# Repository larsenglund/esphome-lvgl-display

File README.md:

ESPHome LVGL display for Home Assistant

Extends https://github.com/agillis/esphome-modular-lvgl-buttons (Copyright (c) 2024 Andrew Gillis)

## ESPHome Setup

1. Create/activate the project virtual environment (PowerShell example):
	```powershell
	& .\.venv\Scripts\Activate.ps1
	```
2. Make sure `pip` itself is current so it can pull the latest wheels:
	```powershell
	python -m pip install --upgrade pip
	```
3. Install the required Python packages (adds the ESPHome CLI entry point):
	```powershell
	python -m pip install -r packages.txt
	```
	If you prefer the dashboard UI, use `python -m pip install "esphome[dashboard]"` instead of the requirements file.
4. Verify the installation before building firmware:
	```powershell
	python -m esphome version
	```
	A semantic version string confirms the CLI is available; an error about `esphome.__main__` indicates the install did not succeed.
5. Build/flash your node:
	```powershell
	python -m esphome run custom_slider.yaml
	or
	python -m esphome run living-room-display.yaml --device living-room-display.local
	```

Troubleshooting tips:
- Ensure VS Code and ESPHome are both pointing to the same virtual environment (`Ctrl+Shift+P` → `Python: Select Interpreter`).
- Re-run step 3 if the environment changes or the dependency cache is cleared.

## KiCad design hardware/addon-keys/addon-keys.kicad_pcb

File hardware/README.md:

# Add-on boards for the Guition ESP32-S3-4848S040 (rev A)

Two KiCad 10 projects for a board that plugs into the 2x4 header on the back of the panel (where the 230 V power/relay module would go) and hangs below the display:
- `addon-keys`: three keys.
- `addon-encoders`: two rotary encoders.

They share everything except the bar below the display. Every KiCad file is generated by a script, using the pipeline from the LED controller project (`notes/cheap mcu AC632/rgbw-controller`). Edit the scripts, not the KiCad files, and rerun them.

**Status:** schematics, placement and routing done for both boards, DRC clean. Not ordered or built yet, so nothing is tested on a real board.
- **From Guition's own files:** the header pinout and the panel size.
- **Measured on a panel:** the header's position. The measurement agrees with a community replacement back cover to about 0.1 mm.
- **Placeholder:** the tab's outline.

**Revision:** both boards are rev A, marked on the bar's back silkscreen (`addon-keys rev A`, `addon-encoders rev A`) and in the schematic and PCB title blocks. `REV` in `addon/gen_addon.py` sets all of them. A board that changes after one has been made needs a new rev.

The overlays (User.Drawings layer) show the enclosure, its 5 mm border, and the 20 mm keycaps or the 25 mm knobs. The keys board's overlay also shows the enclosure's bottom border with the radar.

## Two boards

Keys and encoders are never fitted together. With the encoders as far apart as the enclosure allows, their pins and tab slots land on the switches' holes and pads in every rotation, about 0.16 mm short at best. So each gets its own board.

- **addon-keys:**
  - Three MX switches (HanElectricity CPG151101D13, clicky) in CPG151101S11-16 hot-swap sockets.
  - A warm-white 1206 LED in each switch's LED slot.
  - The HLK-LD2402 radar on a break-away piece centred below key 2. Snap it off for a build without the radar.
- **addon-encoders:**
  - Two Bourns PEC11R-4215F-S0024 encoders with push switches, for 25 mm knobs.
  - The radar between them. Leave it off for a build without the radar; there is no piece to snap off.
- **Both:**
  - CH32V003A4M6 co-processor, an I2C slave to the panel.
  - A bare SHT40 on a U-tab at the bar's right end.
  - 3.3 V LDO.
  - 5 V in from solder pads or an optional USB-C. The board feeds 5 V to the panel through the 2x4 header, so the panel's own USB is never connected.
  - Spare pins on solder pads (J5) and fourteen test points.

## Board (both)

- **Enclosure (front), as planned:**
  - **Width:** 82.9 mm, 2 mm a side narrower than the wall mount. The keys and encoders are still spaced for an 85.6 mm enclosure, so the side borders are 3.65 mm.
  - **Border:** 5 mm at the top and bottom, then a 1 mm gap around each keycap or knob.
  - **Height:** 32 mm for the keys and 37 mm for the encoders. With the radar, the keys board's enclosure has a radar section below that: 2 mm a side narrower again and half as tall (16 mm), 48 mm in all.
- **Bar (front, facing the room):**
  - **Width:** 79.4 mm, centred on the panel. Test-fitted, it sat flush with the panel's left edge and 0.9 mm short of its right edge. So it was trimmed 0.9 mm on the left to centre it, plus 1.1 mm on each side for the walls. It then lost 2 mm more on each side for the narrower enclosure, which leaves 1.75 mm beside it for the cover's walls and clearance.
  - **Height:** 30.9 mm on the keys board and 35.9 mm on the encoders board, ending 1.1 mm above the 5 mm bottom border.
- **SHT40 U-tab:**
  - **Where:** at the bar's right end, beside key 3 or encoder 2.
  - **Shape:** a 1 mm U-shaped slot cuts out a tongue 21 mm long: 3.1 mm wide on the keys board, 4.65 mm on the encoders board. It hangs from the top and is free at its lower end, near the bottom edge where the enclosure's vents should go.
  - **Parts:** the bare SHT40 near the free end, and C4 (100 nF) on the tongue.
  - **Distance from heat:** far from the regulator, the chip and the radar. On the keys board, key 3's LED, a few milliwatts, is the nearest heat source.
- **Panel:** 86.5 x 86.5 x 13.6 mm, from Guition's dimension drawing.
- **Panel header H1:** a 2x4 female socket with 2.54 mm pitch, its long axis vertical.
  - **Position (measured):** seen from the front, the header body starts 17 mm from the panel's left edge and 22 mm from its bottom edge. With a 5.08 x 10.16 mm body, its centre is 23.71 mm left of and 16.17 mm below the panel's centre.
  - **Cross-check:** the Printables replacement cover 1487412 has its window centred at 23.8 / 16.1 mm.
  - **Pinout (Guition schematic):** 1 GND, 2 GND, 3 IO40 (relay 1), 4 U0RXD, 5 IO2 (relay 2), 6 U0TXD, 7 IO1 (relay 3), 8 5V.
  - **Pin 1:** the top of the column nearer the panel's centre.
  - **No 3.3 V:** H1 has none, so the board has its own regulator.
  - **IO1/IO2/IO40:** they reach H1 through 0 Ω links R25-R27 on the panel. The alternative links R21-R23 route them to the audio amplifier instead.
- **H1 height:** the socket stands about 3 mm out of the panel's back, so the board's front sits 3.2 mm behind the panel's back (the wall mount allows for it).
- **J1:** the male header that plugs into H1. Its footprint numbers each pad like the H1 pin it mates with, so the schematic pin numbers are the panel's. SDA = IO1 (pin 7), SCL = IO2 (pin 5). IO40 and the ESP's UART0 (pins 3, 4, 6) go to the spare pads.
- **Spare pads and test points (back, along the bar's top edge below the tab, behind the enclosure's top border):**
  - **J5:** a row of 2.54 mm through-hole pads for wires or a header, labelled on the back. In order: IO40, RXD and TXD (the ESP's UART0, which carries its boot log), PA2 and PD7 (the co-processor's spare pins; PD7 doubles as NRST), and GND.
  - **TP1-TP8:** 1.5 mm pads on the back, 3 mm apart: 5V, 3V3, GND, SDA, SCL and the radar's TX, RX and OUT (labelled R-TX, R-RX, R-OUT). On the keys board the radar's three are in the order R-OUT, R-TX, R-RX, the order their tracks arrive in. They stay on the bar when the keys board's radar piece is snapped off.
  - **TP9-TP14:** 1.5 mm pads on the back for the keys' or encoders' own signals, each labelled beside it. They sit where the back has room next to those tracks, so they aren't all in the row:
    - **Keys board:** K1, K2 and K3 below the row, LED2 and LED3 above it on the tab, and LED1 further up the tab, between the co-processor and the resistors.
    - **Encoders board:** E1_SW, E1_B and E1_A in a second row below J5, E2_A and E2_B at the right-hand end of the row, and E2_SW above the 5V pad.
- **Alignment holes MH1 and MH2:** 2.2 mm, no copper, 37 mm left and right of the centre and 4.5 mm below the panel's bottom edge, for the wall mount's 2 mm pins.
- **Tab (behind the panel):**
  - **Size and position:** 28.5 mm wide. Its left edge stays clear of the stock back cover's screw near the panel's lower-left corner (front view, about 37 mm left of and 29 mm below the centre).
  - **Hook notch:** its lower-left corner is cut away, 3.6 mm across and 5.75 mm up from the panel's bottom edge, for the wall mount's lower-left clip hook (30.85 mm left of and 38.5 mm below the panel's centre). The resistor row starts right of it.
  - **Front:** the 2x4 header only.
  - **Back (wall side, inside the wall box):** the USB-C (opening at the tab's right edge), the 5 V wire pads, the LDO, the co-processor, the resistors and the programming pads. Keeping the heat sources here keeps them away from the SHT40.
- **Hand soldering:**
  - 1206 hand-solder pads.
  - SOT-223 regulator.
  - SOIC-16 with pads 0.8 mm longer than standard.
  - Through-hole headers and encoders.
  - The hot-swap socket pads are 2.5 x 2.55 mm.
  - The exception is the bare SHT40, a 1.5 mm DFN with its pads underneath. Its footprint has pads 0.5 mm longer than standard, so it can be tinned and reflowed from outside, but hot air or a hot plate is the reliable way. A small breakout could fit on the tongue instead if you prefer.

## Routing (both)

2 layers, 1 oz. `addon/route_addon.py` runs all of it.

- **Track widths:** `+5V` 0.5 mm, since it feeds the panel too. `+3V3` and GND 0.3 mm (about 100 mA). Signals 0.25 mm. Clearance 0.2 mm.
- **GND:** a pour on each side, joined by stitching vias about 7 mm apart. Every surface-mount GND pad has its own via, and J4's GND pad is tied to TP3 on the back, so signal tracks can't fence a pad off from the pours. Freerouting doesn't wire GND.
- **Vias:** tented on both sides. None inside pads, as those are soldered by hand.
- **SHT40 tongue:** routed by hand, with its own 0.25 mm tracks up the back and no pour on either side, so little heat reaches the sensor along the copper.
- **Everything else:** Freerouting, best of several runs, then a small A* router for anything left open. It runs on both sides of the board, including under the switches and encoders; the copper there is covered by solder mask.
- **TP9-TP14:** added to the routed boards afterwards, on or beside the tracks already there, with short tracks and one via (LED1's, on the keys board). A fresh `route_addon.py` run puts them in the same spots and routes them like any other net.

## Keys board

- **Keys:** three, spread evenly inside the border, so they are 26.8 mm apart, centred 16 mm below the panel's bottom edge. Switches turned 90 degrees, so the socket pads on the back stay inside each switch's outline and the LED slot faces right.
- **Radar (break-away piece):**
  - **Position:** centred on the bar, under key 2, as close to the keys as the switches allow. Its top edge is 0.3 mm below key 2's switch body, so its top 2.7 mm sit behind keycap 2 and the gap around it. It can't come any closer: the switch body is in the way, and between the keys there is only 12.8 mm for the 20 mm module. The bottom border with the radar shrinks to about 17.4 mm.
  - **Effect of key 2:** key 2's switch stands about 11.6 mm tall right at the radar's top edge. That shades part of its upward view; the forward view isn't affected.
  - **Break line:** steps up under the radar to just below key 2's socket, notching the middle of the bar's bottom edge, with a 1 mm gap down each side of the piece. With the piece snapped off, the notch hides behind the 5 mm border.
  - **Bridges:** three 4 mm bridges with 0.5 mm mouse-bite holes on the bar's edge line: one across each side gap and one across the top gap, right of key 2's hot-swap socket (there is no room for one on its left). The left bridge, by the radar's header column, has only its two end holes, and the radar's five tracks cross it between them, straight and all on the back: score the back with a knife before snapping, and clean up the track ends so they can't short. The pours stay off all three bridges.
  - **Radar tracks:** routed by hand from the header, across the bridge and up the back of the bar left of key 2, then along above the key sockets to the test points. The radar's GND drops to the front pour through a via just left of the bridge.
  - **Orientation:** turned 180 degrees from Hi-Link's figure 6-1, so all five header pins land on the piece; Hi-Link's manual says this orientation is equivalent. The module floats over the notch and the bridges on its 2.5 mm header.
- **SHT40:** sits below the 1 mm gap between keycap 3 and the border.

## Encoders board

- **Encoders:** as far apart as the enclosure allows. Across, it is 5 mm border, 1 mm gap, knob, the space between, knob, 1 mm gap, 5 mm border, so the centres are 18.5 mm in from each end of the enclosure and 48.6 mm apart.
- **Height:** the same from top to bottom, so the enclosure is 37 mm tall and the bar 5 mm taller than the keys board's. The encoders are centred 18.5 mm below the panel's bottom edge, 2.5 mm lower than the keys.
- **Radar:** midway between the encoders and level with them, oriented as in Hi-Link's figure 6-1 (header column on the right). Seen from the front, the knobs clear its sides by about 1.8 mm. Plastic knobs are best; metal ones beside the radar would shade its view to the sides.
- **SHT40:** below and to the right of knob 2, in the enclosure's lower-right corner, with C4 above it. Both are clear of the knob.

## Pin map (CH32V003A4M6)

| Pin | Keys board | Encoders board |
|---|---|---|
| PC1 / PC2 | I2C SDA / SCL to the panel (GPIO1 / GPIO2), 4.7k pull-ups | same |
| PD5 / PD6 | USART1 TX / RX to the radar | same |
| PD4 | radar OUT (presence) | same |
| PC6 / PC7 / PC0 | LED 1 / 2 / 3, PWM on TIM1 CH1-CH3 (remap 1) through 100 R | encoder 1 A / B, encoder 2 A |
| PC3 / PA1 / PC4 | key 1 / 2 / 3 | encoder 1 push / encoder 2 B / encoder 2 push |
| PD1 | SWIO (WCH-LinkE on J4) | same |
| PD7, PA2 | spare, on J5 | same |

The two boards use the same pins, so one firmware can serve both. It needs to know which board it's on.

## Parts

| Ref | Part | LCSC | Board |
|---|---|---|---|
| U1 | LDL1117S33R, 3.3 V LDO, SOT-223 | C435835 | both |
| U2 | CH32V003A4M6, SOP-16 | C5346357 | both |
| U3 | HLK-LD2402 radar | C48935081 | both, optional |
| SW1-SW3 | CPG151101S11-16 hot-swap socket + CPG151101D13 switch | C41430893 + C49234235 | keys |
| D1-D3 | warm-white 1206 LED, 2800-3400 K (XINGLIGHT XL-3216WWC) | C965830 | keys |
| R5-R7 | 100 R 1206 | C17901 | keys |
| ENC1, ENC2 | Bourns PEC11R-4215F-S0024 | C143790 | encoders |
| C1, C2 | 10 uF 1206 | C7467044 | both |
| C3 | 100 nF 1206 | C93194 | both |
| R3, R4 | 4.7k 1206 (I2C pull-ups) | C17936 | both |
| J1 | 2x4 male header, 2.54 mm, into the panel's H1 (pin length: see below) | C492421 | both |
| J2 | 5 V wire pads | | both |
| J3, R1, R2 | USB-C 6P power-only, 4.7k CC pull-downs (5.1k +-20 %) | C456012, C17936 | both, optional |
| J4 | programming pads: SWIO, 3V3, GND | | not fitted |
| J5 | spare pads: IO40, RXD, TXD, PA2, PD7, GND | | not fitted |
| TP1-TP14 | test points, bare 1.5 mm pads | | both, no part |
| U5 | Sensirion SHT40-AD1B-R2 (I2C 0x44), DFN-4 1.5 x 1.5 mm. Not in LCSC's shop: see below | C2909890, for JLCPCB fitting it; DigiKey 1649-SHT40-AD1B-R2CT-ND to solder by hand | both |
| C4 | 100 nF 1206, on the SHT40 tab | C93194 | both |

## Before ordering

- **Header position:** worth a careful second measurement before ordering, since a board-to-board connector leaves no slack. It is set by `HDR_DX` and `HDR_DY` in `place_addon.py`.
- **Panel links:** check that R25-R27 (0 Ω) are fitted on your panels, so IO1 and IO2 actually reach H1. That is likely on relay units and should be checked on ones bought without relays.
- **Pin length:** H1 stands about 3 mm out of the panel's back and the board's front is 3.2 mm behind that back, so H1's mouth is only 0.2 mm from the board's front. That leaves no room for a header's 2.5 mm plastic spacer or for a solder fillet on the front. So use a standard 2x4 header (C492421: 6 mm pins, 2.5 mm spacer, 3 mm tails) like this: push the tails in from the front, solder on the back, pull the spacer off over the pin tips, then cut the pins to about 6 mm past the board's front. That goes about as deep into H1 as a normal header would. H1's actual depth hasn't been measured, so check it with a loose pin before cutting. A long-pin header with its spacer on the back, such as C7128766 (8.13 mm pins), also reaches, but it has to be soldered on the front or with the spacer held off the back.
- **Mechanics:** check how the board gets past the frame rim, and the outline.
- **Radar pinout:** check the module's print against 1 VCC, 2 OUT, 3 GND, 4 TX, 5 RX (Hi-Link manual p. 7).
- **Radar header:** the radar's pins must come out of the non-antenna side.
- **LED fit:** check that a 1206 LED fits in the switch's LED slot. From the datasheet the slot is about 9.4 x 2.7 mm.
- **SHT40:** LCSC's shop doesn't sell Sensirion's part. C2909890 only works for having JLCPCB fit it (16,586 in its parts data on 2026-11-02). To solder it by hand, buy DigiKey 1649-SHT40-AD1B-R2CT-ND: cut tape, 3,379 in stock and 17.11 kr each for 5 or more on 2026-11-02. Either plan how to solder it (hot air or a hot plate) or have JLCPCB fit just that part. LCSC does sell look-alikes named SHT40, untested here. The datasheet of Nyfea's SHT40-N-NF (C54946589, about $1) states the same address (0x44), pin order and measure command (0xFD); C55170371 and C54823945 are others.
- **Alignment test:** print `addon-keys/mockup/addon-keys-alignment.stl` or `addon-encoders/mockup/addon-encoders-alignment.stl` (`tools/export_jig_stl.py`), hot-glue a 2x4 header into it and try it on a panel. Its pin holes are opened up for printing: 1.7 mm for the 2.54 mm headers (J1, J4, J5, radar), 1.5 mm for the encoder pins, the encoder tab slots by 0.2 mm, and 2.9 mm for the wall mount's 2.0 mm alignment pins (MH1, MH2; 2.2 mm on the board).
- **JLCPCB's limits (checked against its capabilities page, 2026-10-31):** tracks, clearances, vias and annular rings are all inside them, with no surcharge for via size. Three things fall outside its guidance: the silkscreen labels are 0.8 mm tall against a 1.0 mm minimum (still 0.15 mm lines, so they should print, just small); the encoders' plated tab slots (1.9 x 2.7 mm) are shorter than the twice-their-width it asks for; and the keys board's mouse-bite bridges are 4 mm against 5 mm for its panel tabs, though it doesn't say that applies inside one design.
- **Parts lists:** [addon-keys/lcsc-order-5.csv](addon-keys/lcsc-order-5.csv) and [addon-encoders/lcsc-order-5.csv](addon-encoders/lcsc-order-5.csv) are LCSC BOM uploads for 5 boards with spares, checked against LCSC's stock, minimums and prices on 2026-11-02 (the keys board's LEDs on 2026-11-17). They come to about $14 and $33, plus $15 if you take the 5 radars on each list: LCSC only has 11, so delete that line for any you already have. Not on them: U5 (LCSC doesn't sell it; see above), keycaps and knobs, and pins for the radar if yours comes without. J4 and J5 aren't fitted.
- **Order files:** `tools/export_gerbers.py` writes `addon-<board>/production/addon-<board>-gerbers.zip` (git-ignored). Export again after any change to the board. There's no placement file yet, in case JLCPCB is to fit any parts.
- **Firmware:** still to write: the CH32V003 firmware and the ESPHome component that talks to it.

## Files

| File | What |
|---|---|
| `addon/gen_addon.py` | Schematic for either board (`keys` or `encoders`): parts, values, LCSC numbers, nets |
| `addon/place_addon.py` | Board for either board: outline (with the U-tab, and the keys board's break-away piece), placement, labels, DRC rules, enclosure overlay, pours, the GND vias and the tracks routed by hand |
| `addon/route_addon.py` | Routes either board from scratch with the tools below |
| `addon/sym-lib-table`, `addon/fp-lib-table` | Library tables, copied into each project by `gen_addon.py` |
| `addon-keys/`, `addon-encoders/` | Generated KiCad projects |
| `addon-*/renders/` | 3D renders (top, bottom, angled) and the enclosure overlay |
| `lib/addon.*` | Symbols, footprints and STEP models |
| `tools/addon_lib.py` | Makes the radar symbol and footprint, the hot-swap MX, PEC11R, SHT40 and hand-solder SOIC-16 footprints, the mouse bites, and the USB-C footprint |
| `tools/export_jig_stl.py` | The fit-test STL, with the pin holes opened up for printing |
| `tools/stitch.py` | Stitching vias between the GND pours, after routing |
| `tools/export_gerbers.py` | The Gerber and drill zip to upload to the fab |
| `tools/autoroute.py`, `tools/finish_route.py`, `tools/fanout.py` | Freerouting, the A* router for what it leaves open, and a via for each SMD GND pad, from fablights. These know these boards aren't rectangles |
| `tools/` | schgen, pcbbuild, netcheck, import_lcsc, render3d, from the LED controller project |

## Rebuild

Run from the repo root. `KPY` is KiCad's own Python, used for everything that imports pcbnew. `VENV` is the fablights venv, which has easyeda2kicad. Routing needs `freerouting-*.jar` and a Java 25 runtime (not committed) in `hardware/tools/ext/` or in a fablights checkout next to this repo.

**`place_addon.py` starts the board over, routing included.** After changing anything on the board, route it again. Freerouting varies from run to run, so the tracks will differ each time: look through the result before ordering.

```bash
KPY="/c/Program Files/KiCad/10.0/bin/python.exe"
CLI="/c/Program Files/KiCad/10.0/bin/kicad-cli.exe"
VENV=/c/Users/englund/Documents/GitHub/fablights/tools/.venv/Scripts/python.exe

"$VENV" hardware/tools/import_lcsc.py C456012 C41430893 C49234235 C143790   # STEP models (once)
python hardware/tools/addon_lib.py                                         # own symbols and footprints
"$CLI" fp upgrade --force hardware/lib/addon.pretty
for B in keys encoders; do
  P=hardware/addon-$B/addon-$B
  python hardware/addon/gen_addon.py $B                                    # schematic
  "$CLI" sch upgrade --force $P.kicad_sch
  python hardware/tools/netcheck.py $P.kicad_sch                           # ERC + single-pin nets
  python hardware/addon/route_addon.py $B                                  # board, placement and routing (a few minutes)
  "$CLI" pcb drc --schematic-parity --severity-all -o drc-$B.rpt $P.kicad_pcb
  "$KPY" hardware/tools/render3d.py addon-$B                               # renders/
  "$KPY" hardware/tools/export_jig_stl.py $B                               # fit-test STL (git-ignored)
  python hardware/tools/export_gerbers.py $B                               # Gerbers and drill for the fab (git-ignored)
done
```

**Don't run `kicad-cli sym upgrade` on `lib/addon.kicad_sym`:** kicad-cli 10.0.6 then crashes loading any schematic that embeds the upgraded radar symbol.

**Expected DRC result:**
- `lib_footprint_issues` (32 and 26), which kicad-cli prints because there's no global footprint library table on this machine.
- Nothing else. Rules in `addon-keys.kicad_dru` allow the keys board's intended overlaps: the LEDs inside the switches, and the radar over key 2's edge and the break line. The encoders board needs none.

## Sources

- Guition's support package for the panel, with the schematic (`5-IO pin distribution/2.png`), the dimension drawing (`3-Structure_Diagram/Dimensions.jpg`) and the spec PDF: <https://pan.jczn1688.com/1/ESP32%20module/4.0inch_ESP32-4848S040.zip>
- Header position measured on a panel and cross-checked against the Printables replacement back cover 1487412; board photos at <https://homeding.github.io/boards/esp32s3/panel-4848S040.htm>
- Hi-Link HLK-LD2402 manual (pins p. 7, drawing p. 37, orientation pp. 33-35): <https://www.manualslib.com/manual/4392645/Hi-Link-Hlk-Ld2402.html>
- Bourns PEC11R datasheet: <https://www.bourns.com/docs/Product-Datasheets/PEC11R.pdf>
- HanElectricity CPG151101D13 and CPG151101S11-16 drawings, from LCSC (C49234235, C41430893)

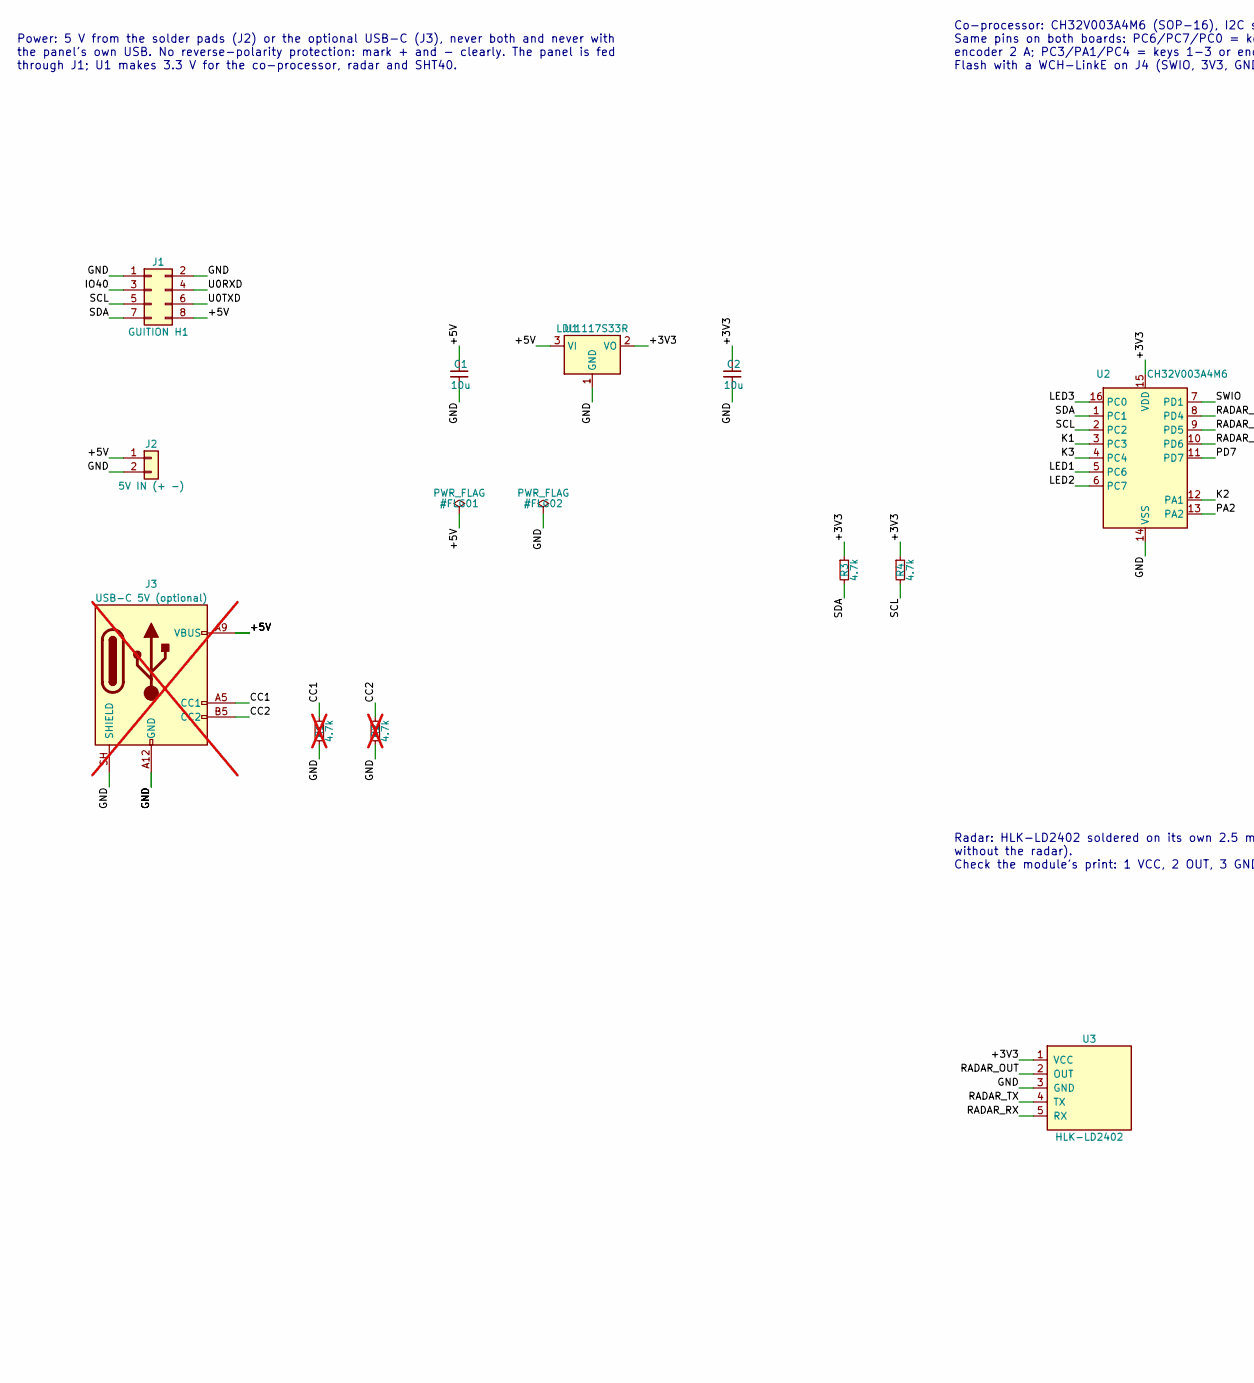
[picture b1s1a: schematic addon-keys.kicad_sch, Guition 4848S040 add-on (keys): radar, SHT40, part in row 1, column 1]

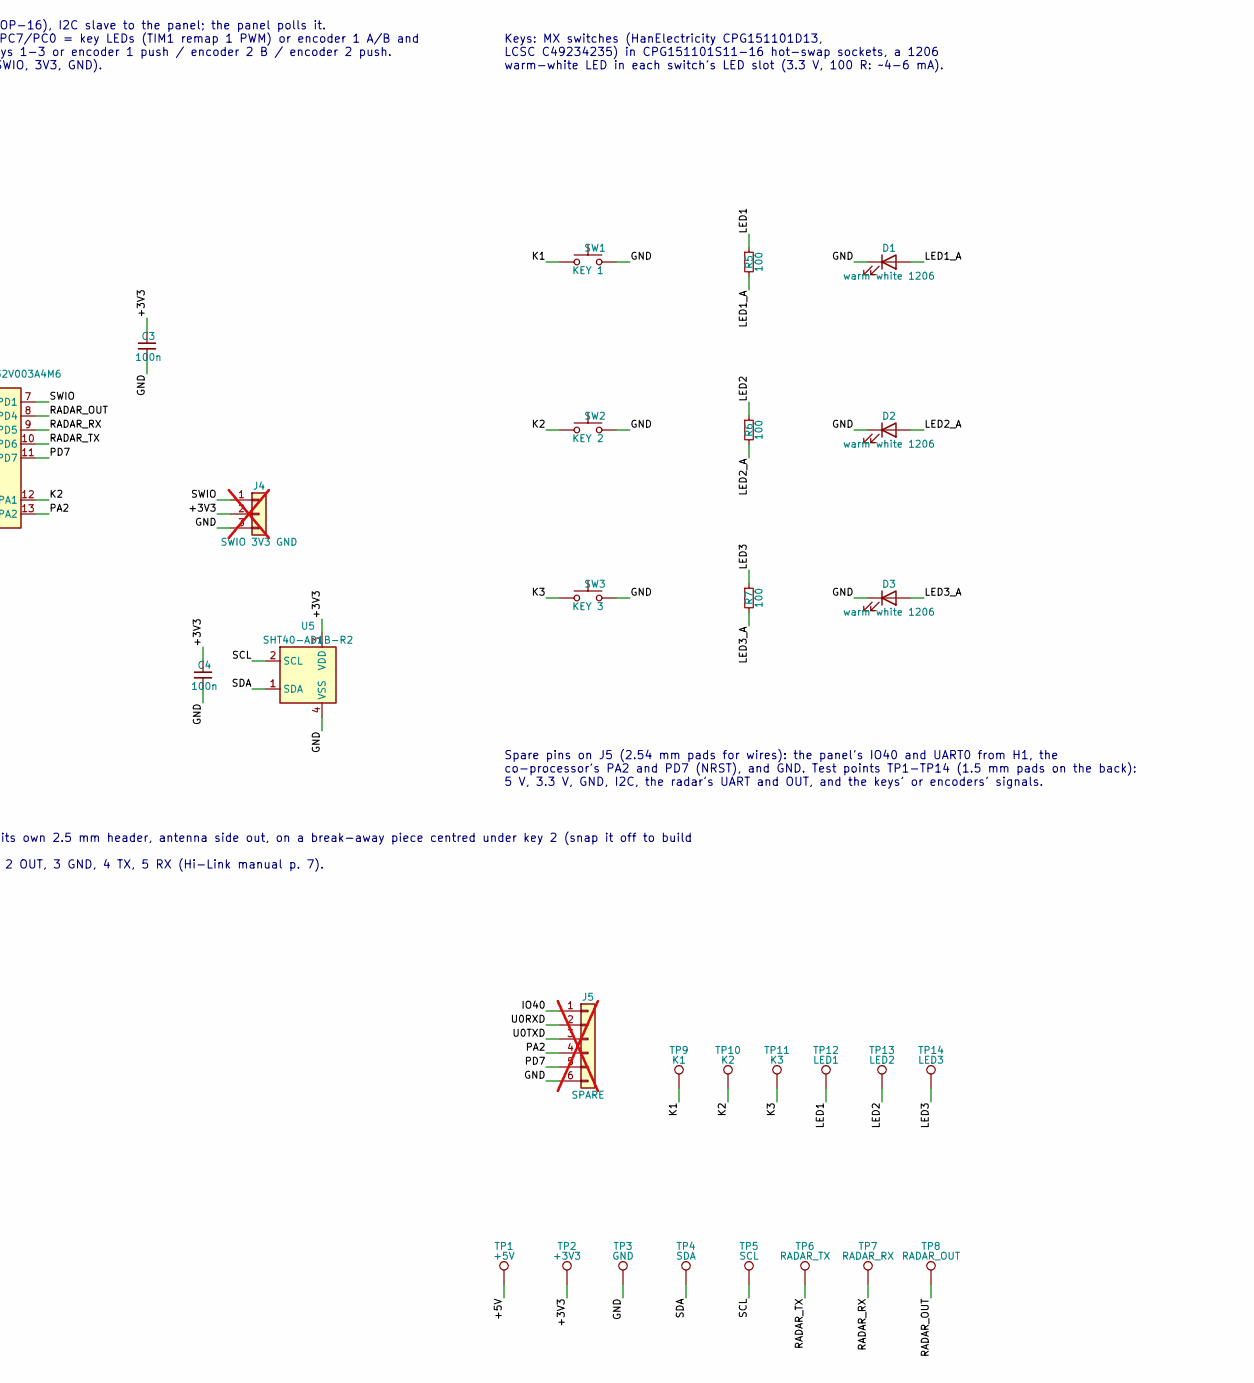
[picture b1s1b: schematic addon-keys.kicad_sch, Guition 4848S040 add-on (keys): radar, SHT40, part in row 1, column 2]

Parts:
C1, C2: 10u; C_1206_3216Metric_Pad1.33x1.80mm_HandSolder; LCSC C7467044
C3, C4: 100n; C_1206_3216Metric_Pad1.33x1.80mm_HandSolder; LCSC C93194
D1, D2, D3: warm white 1206; LED_1206_3216Metric_Pad1.42x1.75mm_HandSolder; LCSC C965830
J1: GUITION H1; Guition_H1_2x04_P2.54mm_Mating; LCSC C492421
J2: 5V IN (+ -); SolderWire-0.5sqmm_1x02_P4.6mm_D0.9mm_OD2.1mm
J3: USB-C 5V (optional); USB_C_Receptacle_SHOU-HAN_TYPE-C-6P; LCSC C456012; not fitted
J4: SWIO 3V3 GND; PinHeader_1x03_P2.54mm_Vertical; not fitted
J5: SPARE; PinHeader_1x06_P2.54mm_Vertical; not fitted
R1, R2: 4.7k; R_1206_3216Metric_Pad1.30x1.75mm_HandSolder; LCSC C17936; not fitted
R3, R4: 4.7k; R_1206_3216Metric_Pad1.30x1.75mm_HandSolder; LCSC C17936
R5, R6, R7: 100; R_1206_3216Metric_Pad1.30x1.75mm_HandSolder; LCSC C17901
SW1: KEY 1; SW_MX_Hotswap_CPG151101S11; LCSC C41430893
SW2: KEY 2; SW_MX_Hotswap_CPG151101S11; LCSC C41430893
SW3: KEY 3; SW_MX_Hotswap_CPG151101S11; LCSC C41430893
TP1: +5V; TestPoint_Pad_D1.5mm
TP2: +3V3; TestPoint_Pad_D1.5mm
TP3: GND; TestPoint_Pad_D1.5mm
TP4: SDA; TestPoint_Pad_D1.5mm
TP5: SCL; TestPoint_Pad_D1.5mm
TP6: RADAR_TX; TestPoint_Pad_D1.5mm
TP7: RADAR_RX; TestPoint_Pad_D1.5mm
TP8: RADAR_OUT; TestPoint_Pad_D1.5mm
TP9: K1; TestPoint_Pad_D1.5mm
TP10: K2; TestPoint_Pad_D1.5mm
TP11: K3; TestPoint_Pad_D1.5mm
TP12: LED1; TestPoint_Pad_D1.5mm
TP13: LED2; TestPoint_Pad_D1.5mm
TP14: LED3; TestPoint_Pad_D1.5mm
U1: LDL1117S33R; SOT-223-3_TabPin2; LCSC C435835
U2: CH32V003A4M6; SOIC-16_3.9x9.9mm_P1.27mm_HandSolder; LCSC C5346357
U3: HLK-LD2402; LCSC C48935081
U5: SHT40-AD1B-R2; Sensirion_DFN-4_1.5x1.5mm_P0.8mm_SHT4x_HandSolder; LCSC C2909890

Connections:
/+3V3: C2.1, C3.1, C4.1, J4.2, R3.1, R4.1, TP2.1, U1.2 (VO), U2.15 (VDD), U3.1 (VCC), U5.3 (VDD)
/+5V: C1.1, J1.8, J2.1, J3.A9 (VBUS), J3.B9 (VBUS), TP1.1, U1.3 (VI)
/CC1: J3.A5 (CC1), R1.1
/CC2: J3.B5 (CC2), R2.1
/GND: C1.2, C2.2, C3.2, C4.2, D1.1 (K), D2.1 (K), D3.1 (K), J1.1, J1.2, J2.2, J3.A12 (GND), J3.B12 (GND), J3.SH (SHIELD), J4.3, J5.6, R1.2, R2.2, SW1.2, SW2.2, SW3.2, TP3.1, U1.1 (GND), U2.14 (VSS), U3.3 (GND), U5.4 (VSS)
/IO40: J1.3, J5.1
/K1: SW1.1, TP9.1, U2.3 (PC3)
/K2: SW2.1, TP10.1, U2.12 (PA1)
/K3: SW3.1, TP11.1, U2.4 (PC4)
/LED1: R5.1, TP12.1, U2.5 (PC6)
/LED1_A: D1.2 (A), R5.2
/LED2: R6.1, TP13.1, U2.6 (PC7)
/LED2_A: D2.2 (A), R6.2
/LED3: R7.1, TP14.1, U2.16 (PC0)
/LED3_A: D3.2 (A), R7.2
/PA2: J5.4, U2.13 (PA2)
/PD7: J5.5, U2.11 (PD7)
/RADAR_OUT: TP8.1, U2.8 (PD4), U3.2 (OUT)
/RADAR_RX: TP7.1, U2.9 (PD5), U3.5 (RX)
/RADAR_TX: TP6.1, U2.10 (PD6), U3.4 (TX)
/SCL: J1.5, R4.2, TP5.1, U2.2 (PC2), U5.2 (SCL)
/SDA: J1.7, R3.2, TP4.1, U2.1 (PC1), U5.1 (SDA)
/SWIO: J4.1, U2.7 (PD1)
/U0RXD: J1.4, J5.2
/U0TXD: J1.6, J5.3

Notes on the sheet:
Spare pins on J5 (2.54 mm pads for wires): the panel's IO40 and UART0 from H1, the co-processor's PA2 and PD7 (NRST), and GND. Test points TP1-TP14 (1.5 mm pads on the back): 5 V, 3.3 V, GND, I2C, the radar's UART and OUT, and the keys' or encoders' signals.
Power: 5 V from the solder pads (J2) or the optional USB-C (J3), never both and never with the panel's own USB. No reverse-polarity protection: mark + and - clearly. The panel is fed through J1; U1 makes 3.3 V for the co-processor, radar and SHT40.
Radar: HLK-LD2402 soldered on its own 2.5 mm header, antenna side out, on a break-away piece centred under key 2 (snap it off to build without the radar). Check the module's print: 1 VCC, 2 OUT, 3 GND, 4 TX, 5 RX (Hi-Link manual p. 7).
Co-processor: CH32V003A4M6 (SOP-16), I2C slave to the panel; the panel polls it. Same pins on both boards: PC6/PC7/PC0 = key LEDs (TIM1 remap 1 PWM) or encoder 1 A/B and encoder 2 A; PC3/PA1/PC4 = keys 1-3 or encoder 1 push / encoder 2 B / encoder 2 push. Flash with a WCH-LinkE on J4 (SWIO, 3V3, GN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
Keys: MX switches (HanElectricity CPG151101D13, LCSC C49234235) in CPG151101S11-16 hot-swap sockets, a 1206 warm-white LED in each switch's LED slot (3.3 V, 100 R: ~4-6 mA).

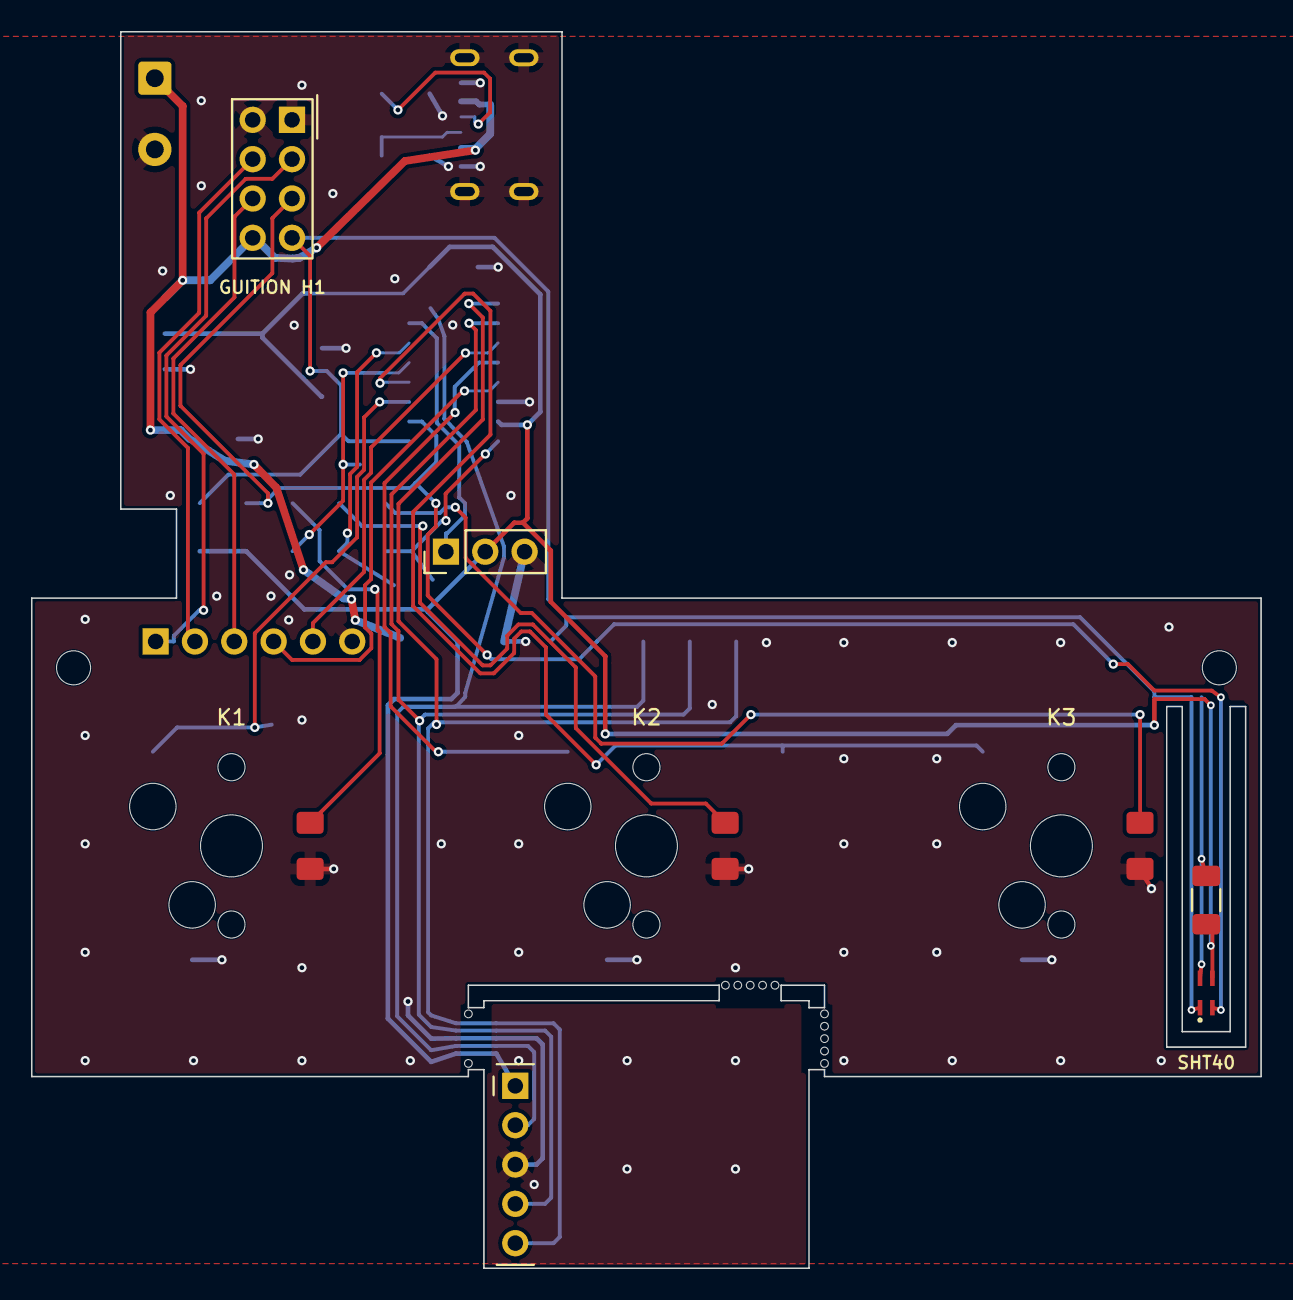
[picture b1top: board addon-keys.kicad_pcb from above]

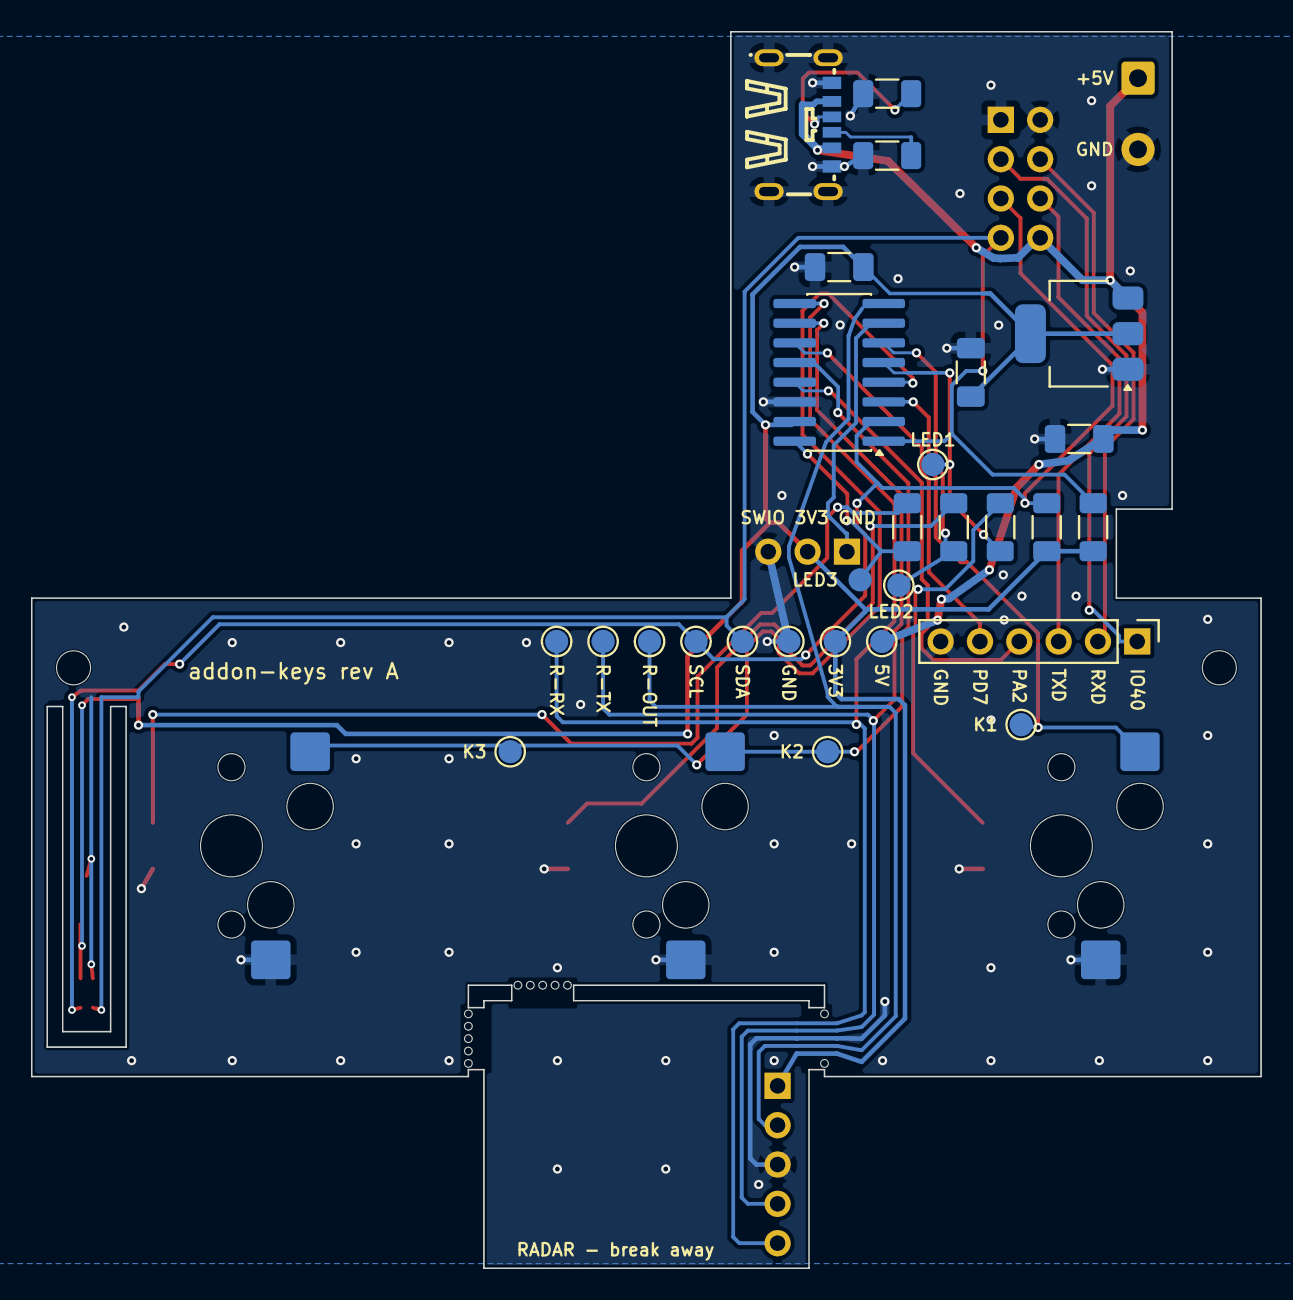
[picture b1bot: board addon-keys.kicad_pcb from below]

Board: 2 copper layers, 79.4 x 79.9 mm, 45 parts (28 on the bottom side), 25 nets.

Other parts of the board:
MB1: MouseBite_4mm_Traces
MB2, MB3: MouseBite_4mm
MH1, MH2: MountingHole_2.2mm_M2

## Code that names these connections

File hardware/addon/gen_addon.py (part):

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3.3 V LDO, 5 V in from solder pads or an optional USB-C, and the panel powered
through the header. The co-processor's pins do the same jobs on both boards
(one firmware, told which board it is on). The header's unused pins (IO40,
UART0) and the co-processor's spare PA2/PD7 come out on pads (J5); test points
on 5 V, 3.3 V, GND, I2C, the radar's lines and the keys' or encoders' signals.
Hand-solder parts throughout (1206, SOT-223, SOIC-16), apart from the SHT40
(1.5 mm DFN: hot air, or extended pads and patience).
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

# Co-processor pins for the keys or encoders (same pins on both boards):
# PC6/PC7/PC0 are TIM1 CH1-CH3 (remap 1): hardware PWM for the key LEDs, and PC6/PC7 are
# TIM1's encoder-mode inputs for encoder 1.
IO = {"keys": {"PC6": "LED1", "PC7": "LED2", "PC0": "LED3", "PC3": "K1", "PA1": "K2", "PC4": "K3"},
      "encoders": {"PC6": "E1_A", "PC7": "E1_B", "PC0": "E2_A", "PC3": "E1_SW", "PA1": "E2_B",
                   "PC4": "E2_SW"}}[BUILD]

# --- power: 5 V in, panel header, 3.3 V LDO -------------------------------------------------
sch.text("Power: 5 V from the solder pads (J2) or the optional USB-C (J3), never both and never with\n"
         "the panel's own USB. No reverse-polarity protection: mark + and - clearly. The panel is fed\n"
         "through J1; U1 makes 3.3 V for the co-processor, radar and SHT40.", (20, 20), size=1.5)
# Pin numbers are the panel's H1 (Guition schematic): 1/2 GND, 3 IO40 (relay 1), 4 U0RXD,
# 5 IO2 (relay 2), 6 U0TXD, 7 IO1 (relay 3), 8 5V. No 3.3 V on H1. IO40/IO2/IO1 reach H1
# through 0R links R25-R27 on the panel (R21-R23 instead send them to the audio amplifier).
sch.add("Connector_Generic:Conn_02x04_Odd_Even", "J1", "GUITION H1", (45, 60),
        fp="addon:Guition_H1_2x04_P2.54mm_Mating", lcsc="C492421",
        pins={"1": "GND", "2": "GND", "3": "IO40", "4": "U0RXD", "5": "SCL", "6": "U0TXD", "7": "SDA",
              "8": "+5V"},
        fields={"Note": "plugs into the panel's H1; SDA = IO1 (pin 7), SCL = IO2 (pin 5); "
                        "IO40 and the ESP's UART0 (pins 3, 4, 6) go to the spare pads J5. "
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
# --- co-processor ------------------------------------------------------------------------------
sch.text("Co-processor: CH32V003A4M6 (SOP-16), I2C slave to the panel; the panel polls it.\n"
         "Same pins on both boards: PC6/PC7/PC0 = key LEDs (TIM1 remap 1 PWM) or encoder 1 A/B and\n"
         "encoder 2 A; PC3/PA1/PC4 = keys 1-3 or encoder 1 push / encoder 2 B / encoder 2 push.\n"
         "Flash with a WCH-LinkE on J4 (SWIO, 3V3, GND).", (190, 20), size=1.5)
sch.add("MCU_WCH_RiscV:CH32V003AxMx", "U2", "CH32V003A4M6", (225, 90),
        fp="addon:SOIC-16_3.9x9.9mm_P1.27mm_HandSolder", lcsc="C5346357",
        pins={"VDD": "+3V3", "VSS": "GND",
              "PC1": "SDA", "PC2": "SCL",
              "PD5": "RADAR_RX", "PD6": "RADAR_TX", "PD4": "RADAR_OUT",
              "PD1": "SWIO", "PD7": "PD7", "PA2": "PA2", **IO},
        fields={"Note": "PD5 = USART1 TX, PD6 = RX; PC1/PC2 = I2C1; PD7 (NRST) and PA2 spare, on J5"})
C("C3", "100n", "C93194", "+3V3", "GND", (255, 70), fields={"Note": "at U2 VDD"})
R("R3", "4.7k", "C17936", "+3V3", "SDA", (170, 110), fields={"Note": "I2C pull-up"})
R("R4", "4.7k", "C17936", "+3V3", "SCL", (180, 110), fields={"Note": "I2C pull-up"})
sch.add("Connector_Generic:Conn_01x03", "J4", "SWIO 3V3 GND", (275, 100), fp=HDR.format(3), dnp=True,
        pins={"1": "SWIO", "2": "+3V3", "3": "GND"}, fields={"Note": "WCH-LinkE programming pads"})
sch.add("Sensor_Humidity:SHT4x", "U5", "SHT40-AD1B-R2", (285, 130),
        fp="addon:Sensirion_DFN-4_1.5x1.5mm_P0.8mm_SHT4x_HandSolder", lcsc="C2909890",
        pins={"SDA": "SDA", "SCL": "SCL", "VDD": "+3V3", "VSS": "GND"},
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
# --- spare pins and test points ------------------------------------------------------------------
sch.text("Spare pins on J5 (2.54 mm pads for wires): the panel's IO40 and UART0 from H1, the\n"
         "co-processor's PA2 and PD7 (NRST), and GND. Test points TP1-TP14 (1.5 mm pads on the back):\n"
         "5 V, 3.3 V, GND, I2C, the radar's UART and OUT, and the keys' or encoders' signals.", (320, 150), size=1.5)
sch.add("Connector_Generic:Conn_01x06", "J5", "SPARE", (335, 195), fp=HDR.format(6), dnp=True,
        pins={"1": "IO40", "2": "U0RXD", "3": "U0TXD", "4": "PA2", "5": "PD7", "6": "GND"},
        fields={"Note": "spare pads: IO40 and UART0 of the panel's ESP (its boot log), PA2 and PD7 of U2"})
for i, net in enumerate(("+5V", "+3V3", "GND", "SDA", "SCL", "RADAR_TX", "RADAR_RX", "RADAR_OUT")):
    sch.add("Connector:TestPoint", f"TP{i + 1}", net, (320 + 11 * i, 240),
            fp="TestPoint:TestPoint_Pad_D1.5mm", pins={"1": net})
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         "Check the module's print: 1 VCC, 2 OUT, 3 GND, 4 TX, 5 RX (Hi-Link manual p. 7).",
         (190, 165), size=1.5)
sch.add("addon:HLK-LD2402", "U3", "HLK-LD2402", (215, 205), fp="addon:HLK-LD2402", lcsc="C48935081",
        pins={"1": "+3V3", "2": "RADAR_OUT", "3": "GND", "4": "RADAR_TX", "5": "RADAR_RX"},
        fields={"Variant": "optional"})

if BUILD == "keys":
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
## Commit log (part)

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2025-11-24 More stuff working
2025-11-28 Add active periods and idle timeout
2025-12-20 Add more displays and cover button
2026-01-10 Added outdoor temp with min and max
